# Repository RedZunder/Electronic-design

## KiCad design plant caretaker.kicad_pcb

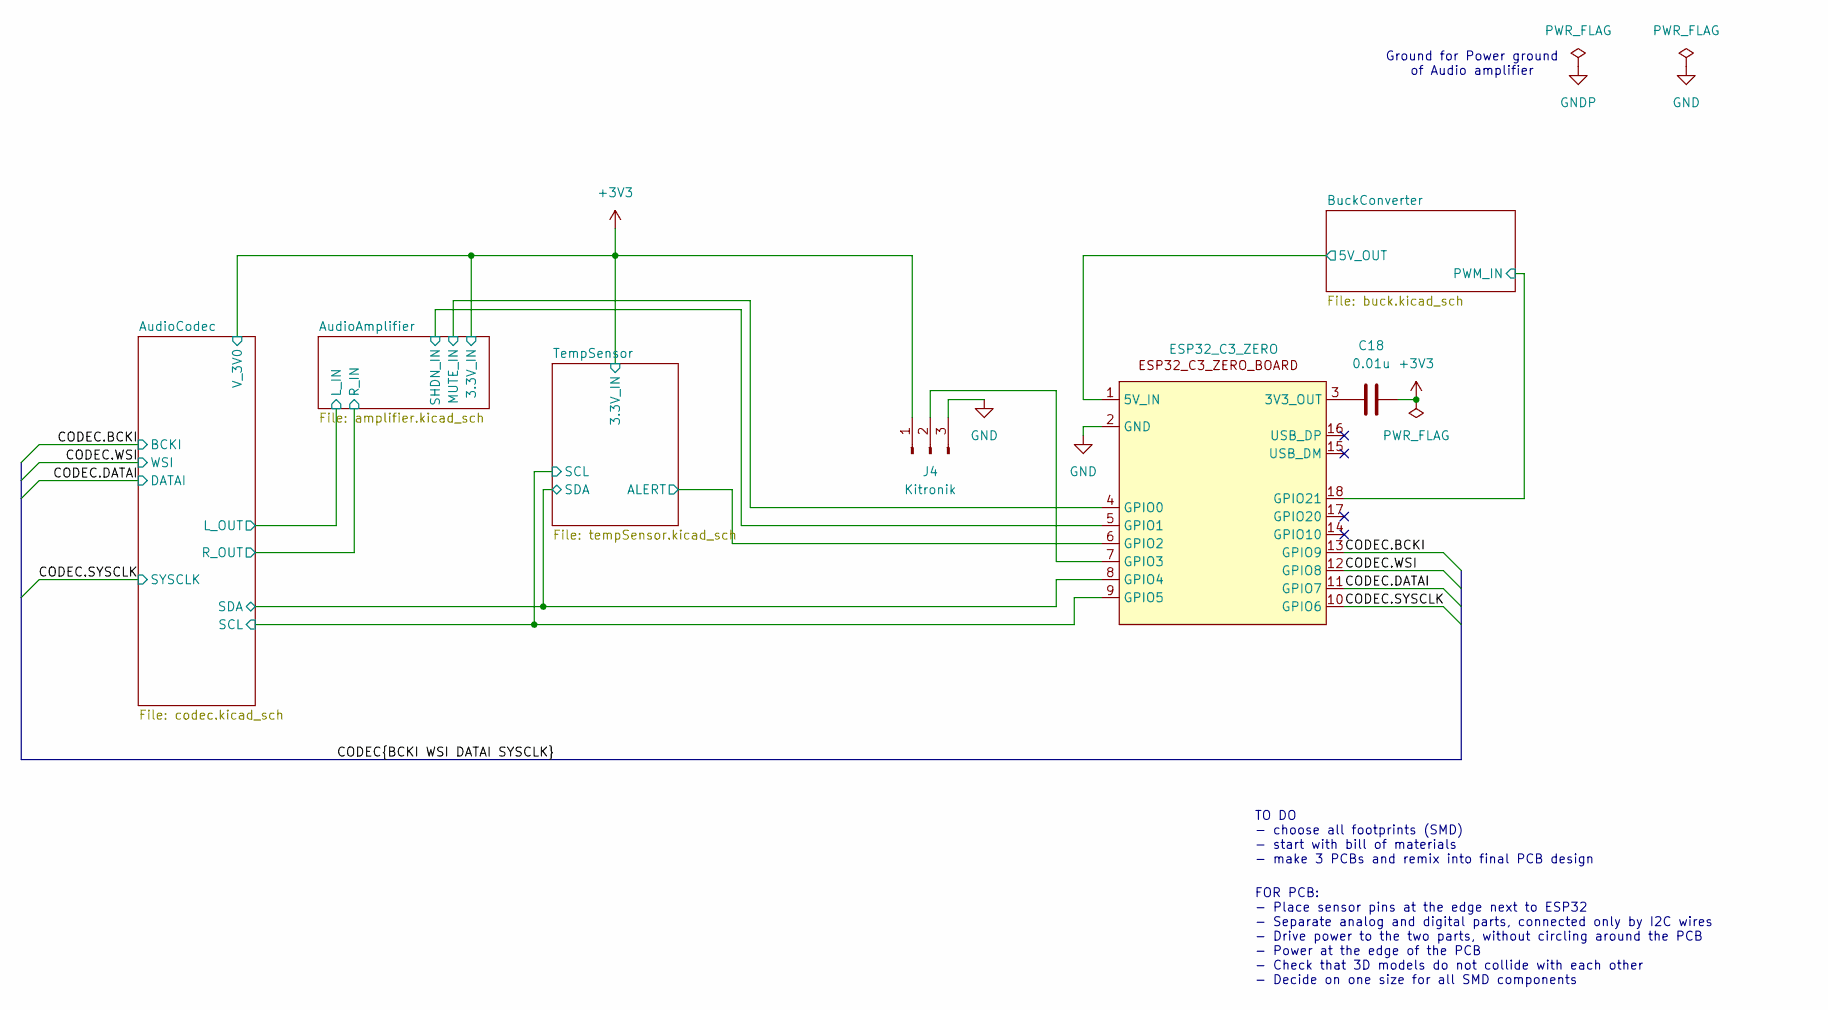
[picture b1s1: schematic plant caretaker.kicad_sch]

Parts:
C18: 0.01u; C_0603_1608Metric
J4: Kitronik; PinHeader_1x03_P2.00mm_Vertical_SMD_Pin1Left
U6: ESP32_C3_ZERO

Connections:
+3V3: C18.2, J4.1; also elsewhere on the board
/AudioAmplifier/MUTE_IN: U6.4 (GPIO0); also elsewhere on the board
/AudioAmplifier/SHDN_IN: U6.5 (GPIO1); also elsewhere on the board
/AudioCodec/SCL: U6.9 (GPIO5); also elsewhere on the board
/AudioCodec/SDA: U6.8 (GPIO4); also elsewhere on the board
/BuckConverter/5V_OUT: U6.1 (5V_IN); also elsewhere on the board
/BuckConverter/PWM_IN: U6.18 (GPIO21); also elsewhere on the board
/CODEC.BCKI: U6.13 (GPIO9); also elsewhere on the board
/CODEC.DATAI: U6.11 (GPIO7); also elsewhere on the board
/CODEC.SYSCLK: U6.10 (GPIO6); also elsewhere on the board
/CODEC.WSI: U6.12 (GPIO8); also elsewhere on the board
/TempSensor/ALERT: U6.6 (GPIO2); also elsewhere on the board
GND: J4.3, U6.2 (GND); also elsewhere on the board
unnamed: J4.2, U6.7 (GPIO3)
unnamed: C18.1, U6.3 (3V3_OUT)

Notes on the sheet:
FOR PCB: - Place sensor pins at the edge next to ESP32 - Separate analog and digital parts, connected only by I2C wires - Drive power to the two parts, without circling around the PCB - Power at the edge of the PCB - Check that 3D models do not collide with each other - Decide on one size for all S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
TO DO - choose all footprints (SMD) - start with bill of materials - make 3 PCBs and remix into final PCB design
Ground for Power ground of Audio amplifier

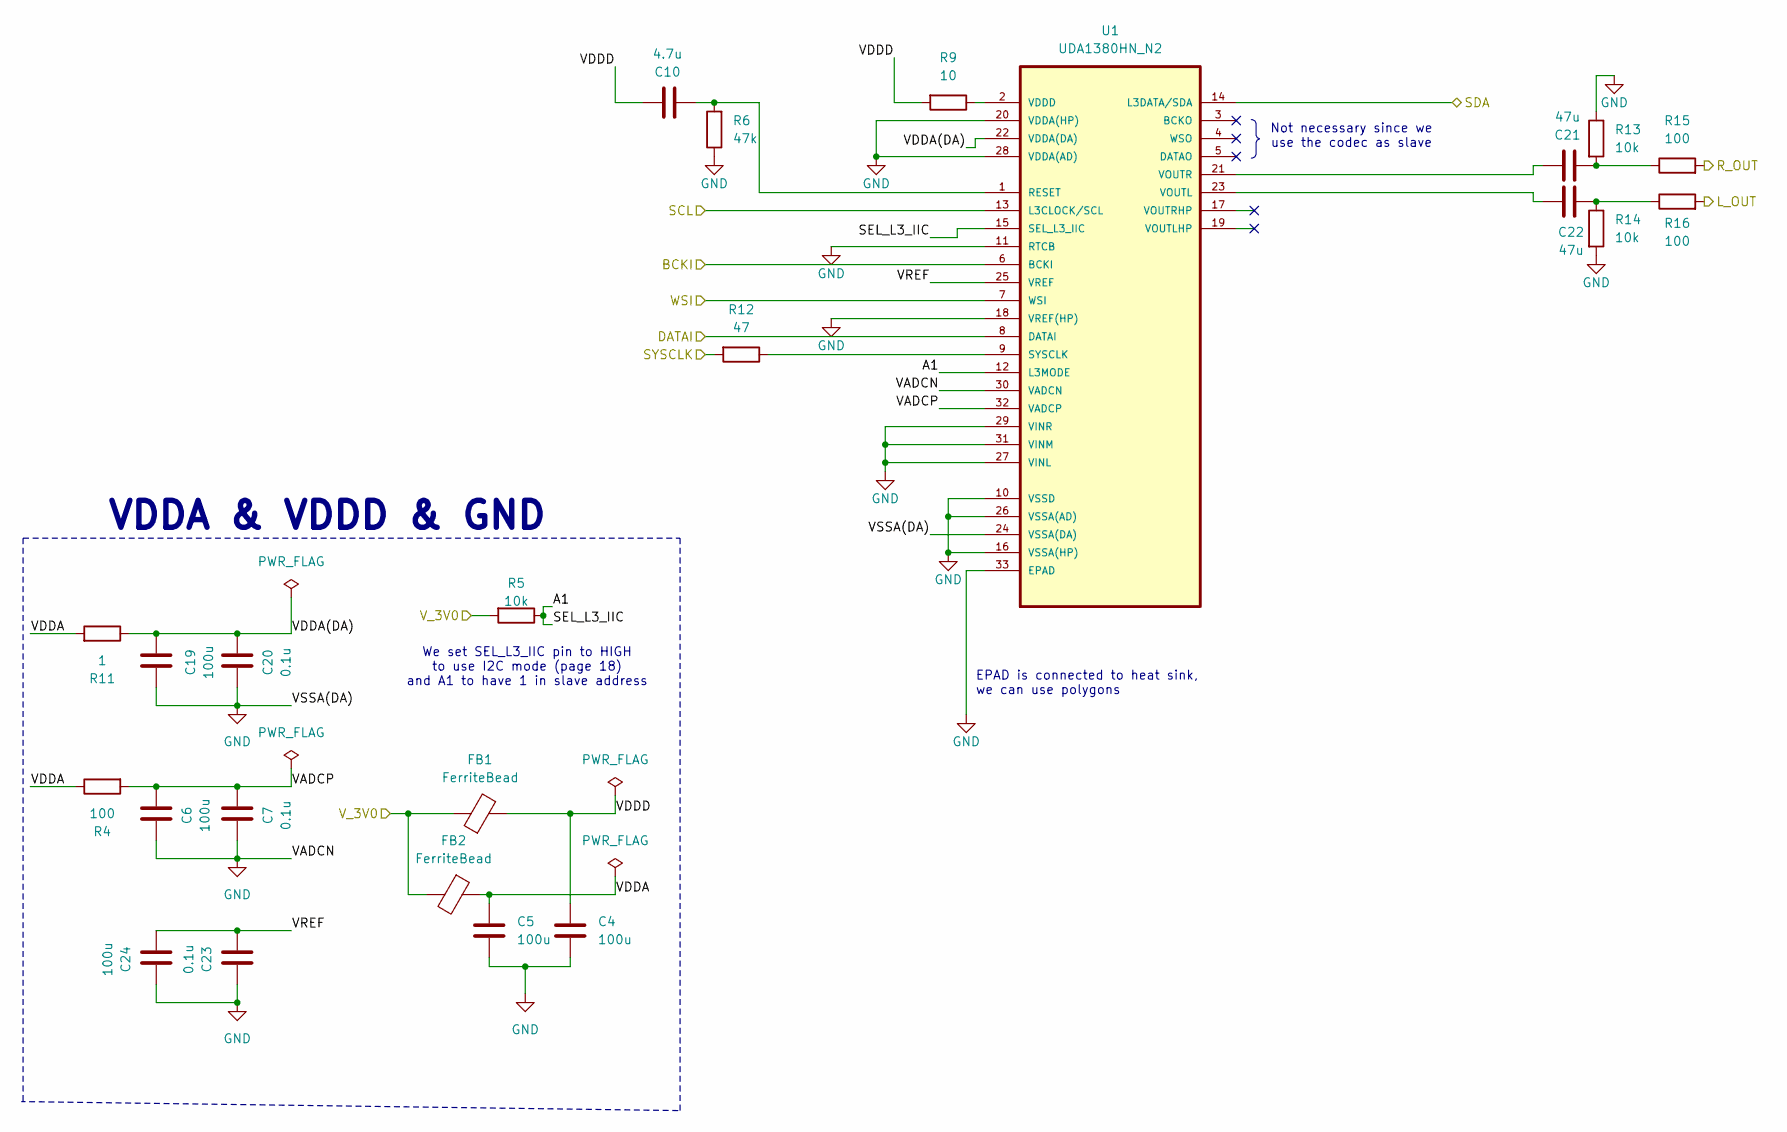
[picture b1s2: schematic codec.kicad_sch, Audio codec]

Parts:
C4, C5, C6, C19, C24: 100u; C_0603_1608Metric
C7, C20, C23: 0.1u; C_0603_1608Metric
C10: 4.7u; C_0603_1608Metric
C21, C22: 47u; C_0603_1608Metric
FB1, FB2: FerriteBead; FerriteBead_742861160_0603
R4, R15, R16: 100; R_0603_1608Metric
R5, R13, R14: 10k; R_0603_1608Metric
R6: 47k; R_0603_1608Metric
R9: 10; R_0603_1608Metric
R11: 1; R_0603_1608Metric
R12: 47; R_0603_1608Metric
U1: UDA1380HN_N2; QFN50P500X500X100-32N

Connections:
+3V3: FB1.1, FB2.2, R5.2; also elsewhere on the board
/AudioAmplifier/L_IN: R16.2; also elsewhere on the board
/AudioAmplifier/R_IN: R15.2; also elsewhere on the board
/AudioCodec/A1: R5.1, U1.12 (L3MODE), U1.15 (SEL_L3_IIC)
/AudioCodec/SCL: U1.13 (L3CLOCK/SCL); also elsewhere on the board
/AudioCodec/SDA: U1.14 (L3DATA/SDA); also elsewhere on the board
/AudioCodec/VADCP: C6.2, C7.2, R4.2, U1.32 (VADCP)
/AudioCodec/VDDA: C5.1, FB2.1, R4.1, R11.2
/AudioCodec/VDDA(DA): C19.2, C20.2, R11.1, U1.22 (VDDA(DA))
/AudioCodec/VDDD: C4.1, C10.1, FB1.2, R9.2
/AudioCodec/VREF: C23.2, C24.2, U1.25 (VREF)
/CODEC.BCKI: U1.6 (BCKI); also elsewhere on the board
/CODEC.DATAI: U1.8 (DATAI); also elsewhere on the board
/CODEC.SYSCLK: R12.2; also elsewhere on the board
/CODEC.WSI: U1.7 (WSI); also elsewhere on the board
GND: C4.2, C5.2, C6.1, C7.1, C19.1, C20.1, C23.1, C24.1, R6.1, R13.1, R14.2, U1.10 (VSSD), U1.11 (RTCB), U1.16 (VSSA(HP)), U1.18 (VREF(HP)), U1.20 (VDDA(HP)), U1.24 (VSSA(DA)), U1.26 (VSSA(AD)), U1.27 (VINL), U1.28 (VDDA(AD)), U1.29 (VINR), U1.30 (VADCN), U1.31 (VINM), U1.33 (EPAD); also elsewhere on the board
unnamed: C21.2, R13.2, R15.1
unnamed: C22.1, R14.1, R16.1
unnamed: C10.2, R6.2, U1.1 (RESET)
unnamed: R12.1, U1.9 (SYSCLK)
unnamed: R9.1, U1.2 (VDDD)
unnamed: C22.2, U1.23 (VOUTL)
unnamed: C21.1, U1.21 (VOUTR)

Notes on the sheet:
We set SEL_L3_IIC pin to HIGH to use I2C mode (page 18) and A1 to have 1 in slave address
VDDA & VDDD & GND
Not necessary since we use the codec as slave
EPAD is connected to heat sink, we can use polygons

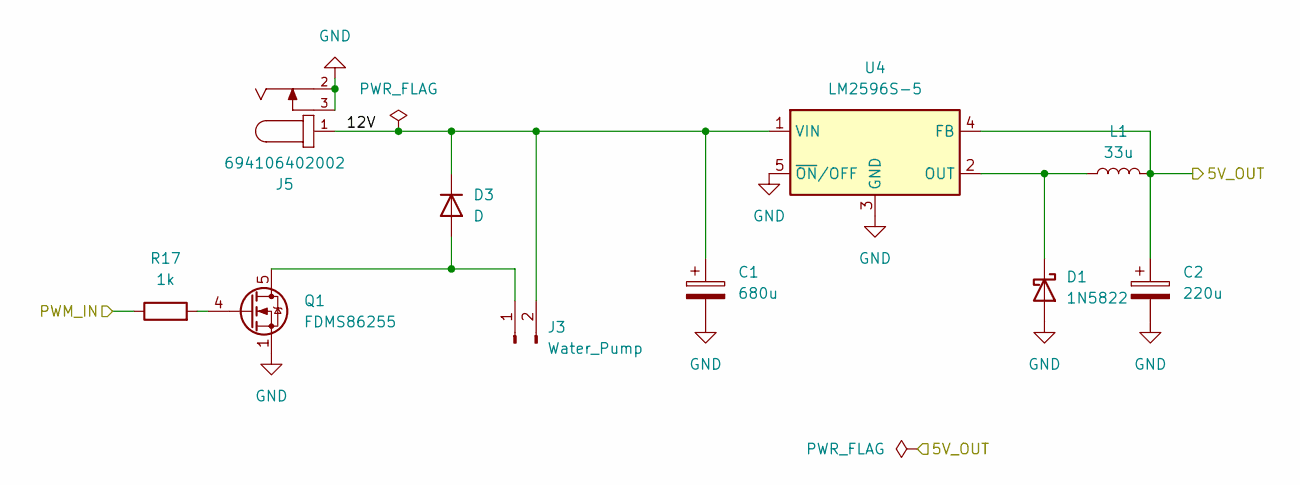
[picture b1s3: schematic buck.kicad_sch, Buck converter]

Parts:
C1: 680u; CP_Elec_10x12.5
C2: 220u; CP_Elec_6.3x7.7
D1: 1N5822; D_0603_1608Metric
D3: D; D_0603_1608Metric
J3: Water_Pump; PinHeader_1x02_P2.00mm_Vertical_SMD_Pin1Left
J5: 694106402002; BarrelJack_Wuerth_694106106102_2.0x5.5mm; PART-NUMBER 694106402002
L1: 33u; L_0603_1608Metric
Q1: FDMS86255; TDSON-8-1
R17: 1k; R_0603_1608Metric
U4: LM2596S-5; TO-263-5_TabPin3

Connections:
/BuckConverter/5V_OUT: C2.1, L1.1, U4.4 (FB); also elsewhere on the board
/BuckConverter/12V: C1.1, D3.1 (K), J3.2, J5.1, U4.1 (VIN)
/BuckConverter/PWM_IN: R17.1; also elsewhere on the board
GND: C1.2, C2.2, D1.2 (A), J5.2, J5.3, Q1.1 (S), Q1.2 (S), Q1.3 (S), U4.3 (GND), U4.5 (~ON/OFF); also elsewhere on the board
unnamed: D1.1 (K), L1.2, U4.2 (OUT)
unnamed: D3.2 (A), J3.1, Q1.5 (D)
unnamed: Q1.4 (G), R17.2

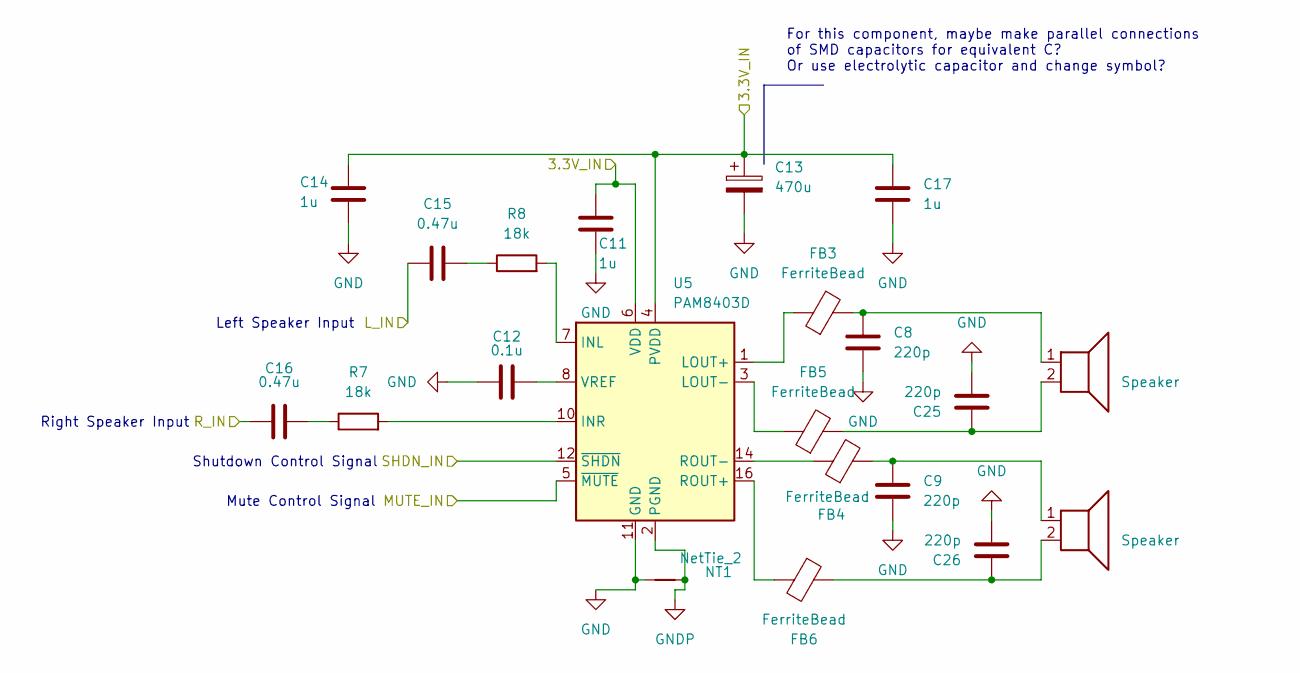
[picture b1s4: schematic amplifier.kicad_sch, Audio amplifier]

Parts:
C8, C9, C25, C26: 220p; C_0603_1608Metric
C11, C14, C17: 1u; C_0603_1608Metric
C12: 0.1u; C_0603_1608Metric
C13: 470u; CP_Elec_8x10.5
C15, C16: 0.47u; C_0603_1608Metric
FB3, FB4, FB5, FB6: FerriteBead; FerriteBead_742861160_0603
LS1, LS2: Speaker; PinHeader_1x02_P2.00mm_Vertical_SMD_Pin1Left
NT1: NetTie_2; Net_Tie_0.2
R7, R8: 18k; R_0603_1608Metric
U5: PAM8403D; SOP-16_3.9x9.9mm_P1.27mm

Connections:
+3V3: C11.1, C13.1, C14.1, C17.1, U5.4 (PVDD), U5.6 (VDD), U5.13 (PVDD); also elsewhere on the board
/AudioAmplifier/L_IN: C15.1; also elsewhere on the board
/AudioAmplifier/MUTE_IN: U5.5 (~MUTE); also elsewhere on the board
/AudioAmplifier/R_IN: C16.1; also elsewhere on the board
/AudioAmplifier/SHDN_IN: U5.12 (~SHDN); also elsewhere on the board
GND: C8.2, C9.2, C11.2, C12.1, C13.2, C14.2, C17.2, C25.2, C26.2, NT1.1, U5.11 (GND); also elsewhere on the board
GNDP: NT1.2, U5.2 (PGND), U5.15 (PGND)
unnamed: C8.1, FB3.2, LS1.1
unnamed: C9.1, FB4.2, LS2.1
unnamed: C15.2, R8.1
unnamed: C16.2, R7.1
unnamed: C25.1, FB5.2, LS1.2
unnamed: C26.1, FB6.1, LS2.2
unnamed: R8.2, U5.7 (INL)
unnamed: R7.2, U5.10 (INR)
unnamed: FB3.1, U5.1 (LOUT+)
unnamed: FB5.1, U5.3 (LOUT-)
unnamed: FB6.2, U5.16 (ROUT+)
unnamed: FB4.1, U5.14 (ROUT-)
unnamed: C12.2, U5.8 (VREF)

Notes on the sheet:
Left Speaker Input
Mute Control Signal
Right Speaker Input
Shutdown Control Signal
For this component, maybe make parallel connections of SMD capacitors for equivalent C? Or use electrolytic capacitor and change symbol?

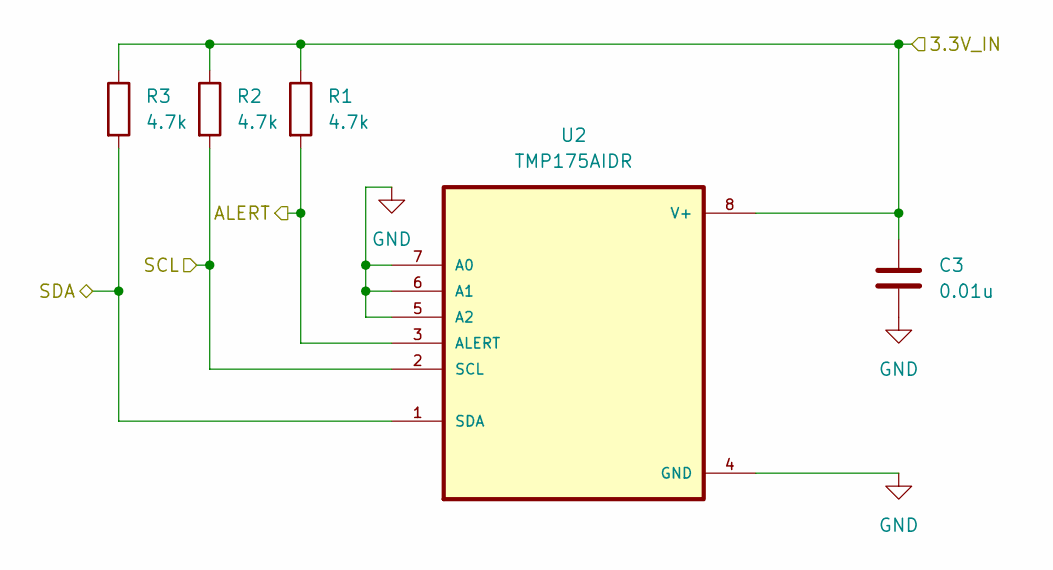
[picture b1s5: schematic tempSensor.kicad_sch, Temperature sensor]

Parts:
C3: 0.01u; C_0603_1608Metric
R1, R2, R3: 4.7k; R_0603_1608Metric
U2: TMP175AIDR; TMP-SOIC127P599X175-8N

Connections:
+3V3: C3.1, R1.1, R2.1, R3.1, U2.8 (V+); also elsewhere on the board
/AudioCodec/SCL: R2.2, U2.2 (SCL); also elsewhere on the board
/AudioCodec/SDA: R3.2, U2.1 (SDA); also elsewhere on the board
/TempSensor/ALERT: R1.2, U2.3 (ALERT); also elsewhere on the board
GND: C3.2, U2.4 (GND), U2.5 (A2), U2.6 (A1), U2.7 (A0); also elsewhere on the board

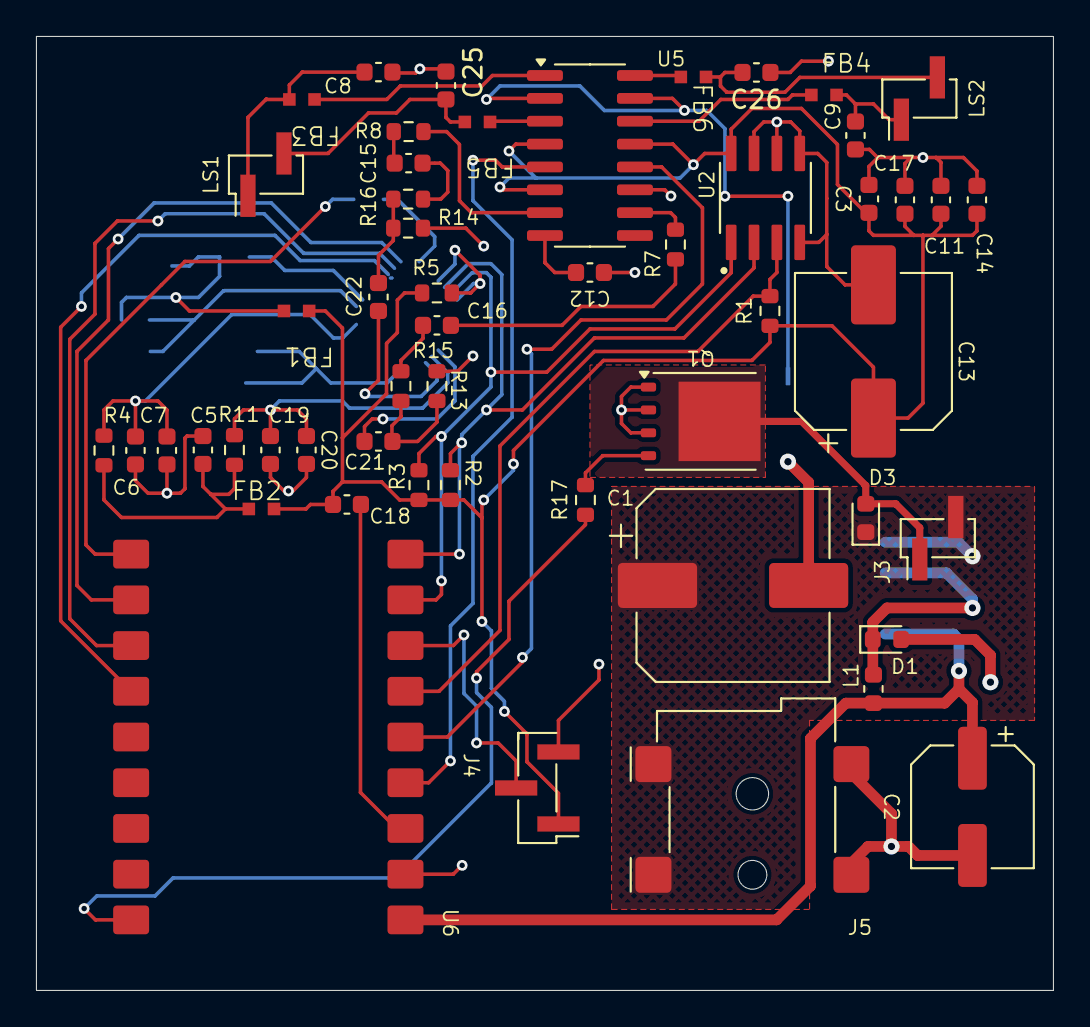
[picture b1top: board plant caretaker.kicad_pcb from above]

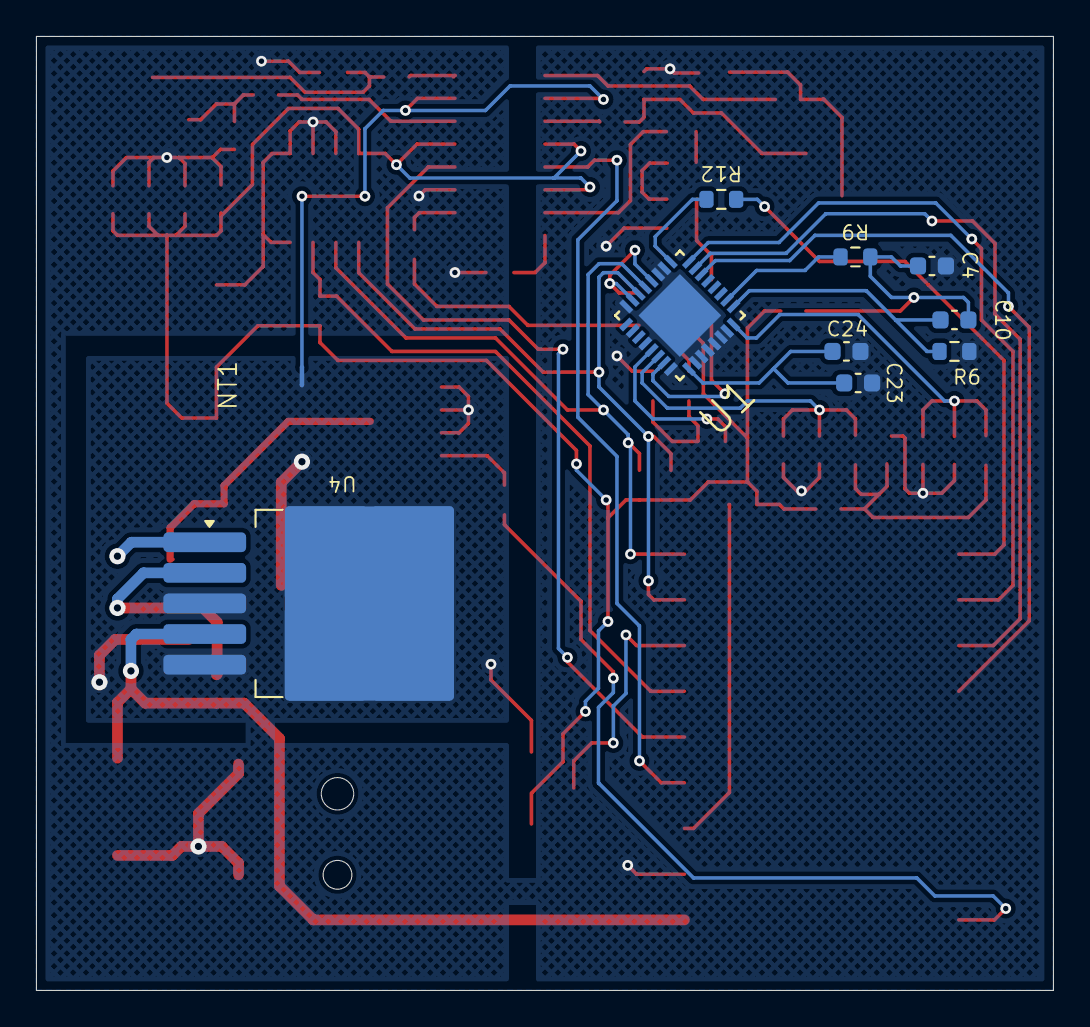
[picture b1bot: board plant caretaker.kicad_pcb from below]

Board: 2 copper layers, 56.5 x 53.0 mm, 63 parts (10 on the bottom side), 48 nets.

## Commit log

2024-12-02 Init
2024-12-02 Added main components
    Added components to the schematic:
    -ESP32-C3
    -TMP175AIDR
    -PAM8403
    -LM2576S-ADJ
2024-12-02 Added connection schematic
    Added connection schematic for Buck Converter
2024-12-02 Added hierarchichal pages
    Now components are divided into pages so that we can change them without merging with each other's files
2024-12-02 testing
2024-12-02 Sheet hierarchy test
    Nothing to see here
2024-12-02 Testing part 2
2024-12-02 Added git ignore
2024-12-05 Added pins to temp sensor
    Hierarchy input/output for the sensor schematic and the root
2024-12-05 Added layout components and comment
    Bypass capacitor and pullup resistors according to datasheet
2024-12-05 Components for audio codec part 1
    reading from data sheet application, page 61
2024-12-08 Made Audio Amplifier Connections
2024-12-09 Added more parts to codec
    VDD and VDDA related pins, and organized a bit
2024-12-09 Organized codec and imported pins
    Also changed color of microchips in main
2024-12-09 Added notes to codec
    About EPAD, microphone and speaker
2024-12-09 Cleanup temperature sensor
    Reconnected grounds and removed useless pins
2024-12-09 Added I2C pins
2024-12-10 Finished AudioAmplifier + Added Values
    Added Buck Coverter components values, finished audio amplifier
2024-12-10 Set 3.3 Output from Buck
2024-12-10 Added microprocessor connections
2024-12-10 TODO list added
2024-12-10 Organized wires a bit
2024-12-10 Fixed connections and digital output of codec
    Used NC instead of GND for output pins
2024-12-10 Added voltage source for testing to main
2024-12-10 Codec finished and added notes
    Corrected input and ouput pins, added NOTES file and cleaned up
2024-12-11 Cleanup, sorting, adding external parts
2024-12-11 Globglobgabgalab
2024-12-11 Added correct microcontroller
2024-12-11 Added Footprint of DJ Jack socket
2024-12-11 Added ESP again
2024-12-11 Corrected pins of ESP32
2024-12-11 Deleted ESP32
    Will make manually the symbol
2024-12-11 New ESP32 symbol 1
2024-12-11 Added a jack for power supply
2024-12-11 Switched model of buck converter
2024-12-11 Connected ESP32 and other components
2024-12-11 Finished connecting ICs to ESP32
    Also fixed bus connection
2024-12-11 Added Lil Pump
2024-12-11 Swapped MOSFET
2024-12-11 Kitronik
2024-12-11 Added Kitronik and cleaned connections
2024-12-11 Created ESP32 footprint pads
2024-12-12 Added basic footprint to ESP32
2024-12-12 Fixed STM32 footprint and added notes
    SMD pads for the microcontroller and TODO list + advice from Bondyra for the design
2024-12-12 Added more notes
2024-12-15 Added footprints and imported to PCB
    All of them except speakers
2024-12-16 Moved Pump to Buck
2024-12-16 Added missing footprints and schemes
2024-12-16 Added TEMPORARY bill of materials
2024-12-16 Moved footprints to proper folder
2024-12-16 Added TMP157 footprint
    Fixed and added the rest of footprints to the PCB
2024-12-16 Added footprints for speakers
    And changed size of other pin headers
2024-12-16 Imported design rules
2024-12-17 Started power connections
2024-12-19 Added power polygon and edge cuts
    Also added 12V label to schematic for polygon net class
2024-12-21 PCB - power connected
2024-12-21 Fixed ESP32 library
2024-12-21 Began connecting digital connections
2024-12-23 Trying different layout for digital part
2024-12-23 Connected more components
2024-12-24 Made more connections
    And re-imported ferrite beads footprints
2024-12-24 Added more connections
    Updated footprints for pin heads and speakers
2024-12-24 Only I2C signals left + cleanup
2024-12-25 Sorted Libraries for other components
2024-12-26 Different version of connections
2024-12-26 Finished PCB
    Also added GNDA and GNDD references, to be changed back to GND later. Also added wires connecting ground polygons
2024-12-27 Optimized connections
2025-01-04 God_bless_this_mess_of_a_PCB
    What is this???? A PCB???? Maby. Maby no? IDK!
2025-01-05 Part of PCB
    Dziękuję Maciej :*
2025-01-05 Added few components to PCB
    :)
2025-01-05 All elements are connected
    :)
2025-01-05 Changed a little
    :)
2025-01-05 I moved one component
2025-01-06 Changes
    :)
2025-01-08 Taest
2025-01-08 Perfection (maybe not)
    :)
2025-01-08 Made it smaller
    Also added power plane for MOSFET
2025-01-08 Changed the size and place of the silkscreens
    :)
2025-01-08 :)
    :)
2025-01-08 Added Power Supply Ground Planes
    :>
2025-01-08 Perfection (propably yes)
    :>
2025-01-08 Fixed a bit
2025-01-08 Moved codec closer to center
2025-01-08 Po konsultacjach
    :>
2025-01-08 Fixed texts
2025-01-08 Made it smaller
    Suddenly I had 81 errors??? Now down to 30 from the codec footprint setup
2025-01-09 Moved the text on F.Silkscreen
    I moved the text because it interfered with the connection :)
2025-01-09 0 errors 0 warnings
2025-01-09 Bondyra's changes
    :>
2025-01-09 Changed grounds and began with new planes
2025-01-09 PCB merge to main
2025-01-11 Finished with ground planes and made board smaller
    WARNING: Unconnected "ground power" for audio amplifier
    Also fixed the ESP32 footprint on board only
2025-01-14 PCB FINISHED - Gerber and drill files exported
2025-01-20 Skibidi toilet
    Sigma boy
